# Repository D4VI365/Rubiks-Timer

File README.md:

# Rubiks Timer
I'm gonna build a timer to use with my rubiks cube, it will be powered by an esp32 and it will host a webpage to view the times registered.

The device is powered by a rechargable 2000mAh LiPo battery, it shows the time to the millisecond and the status of the timer with a strip of neopixels. There also are two phisical buttons for an easier access to deleting the time and adding a penality.

Full timer:

Electrical scheme:

PCB layout: 

Inernal components placement:

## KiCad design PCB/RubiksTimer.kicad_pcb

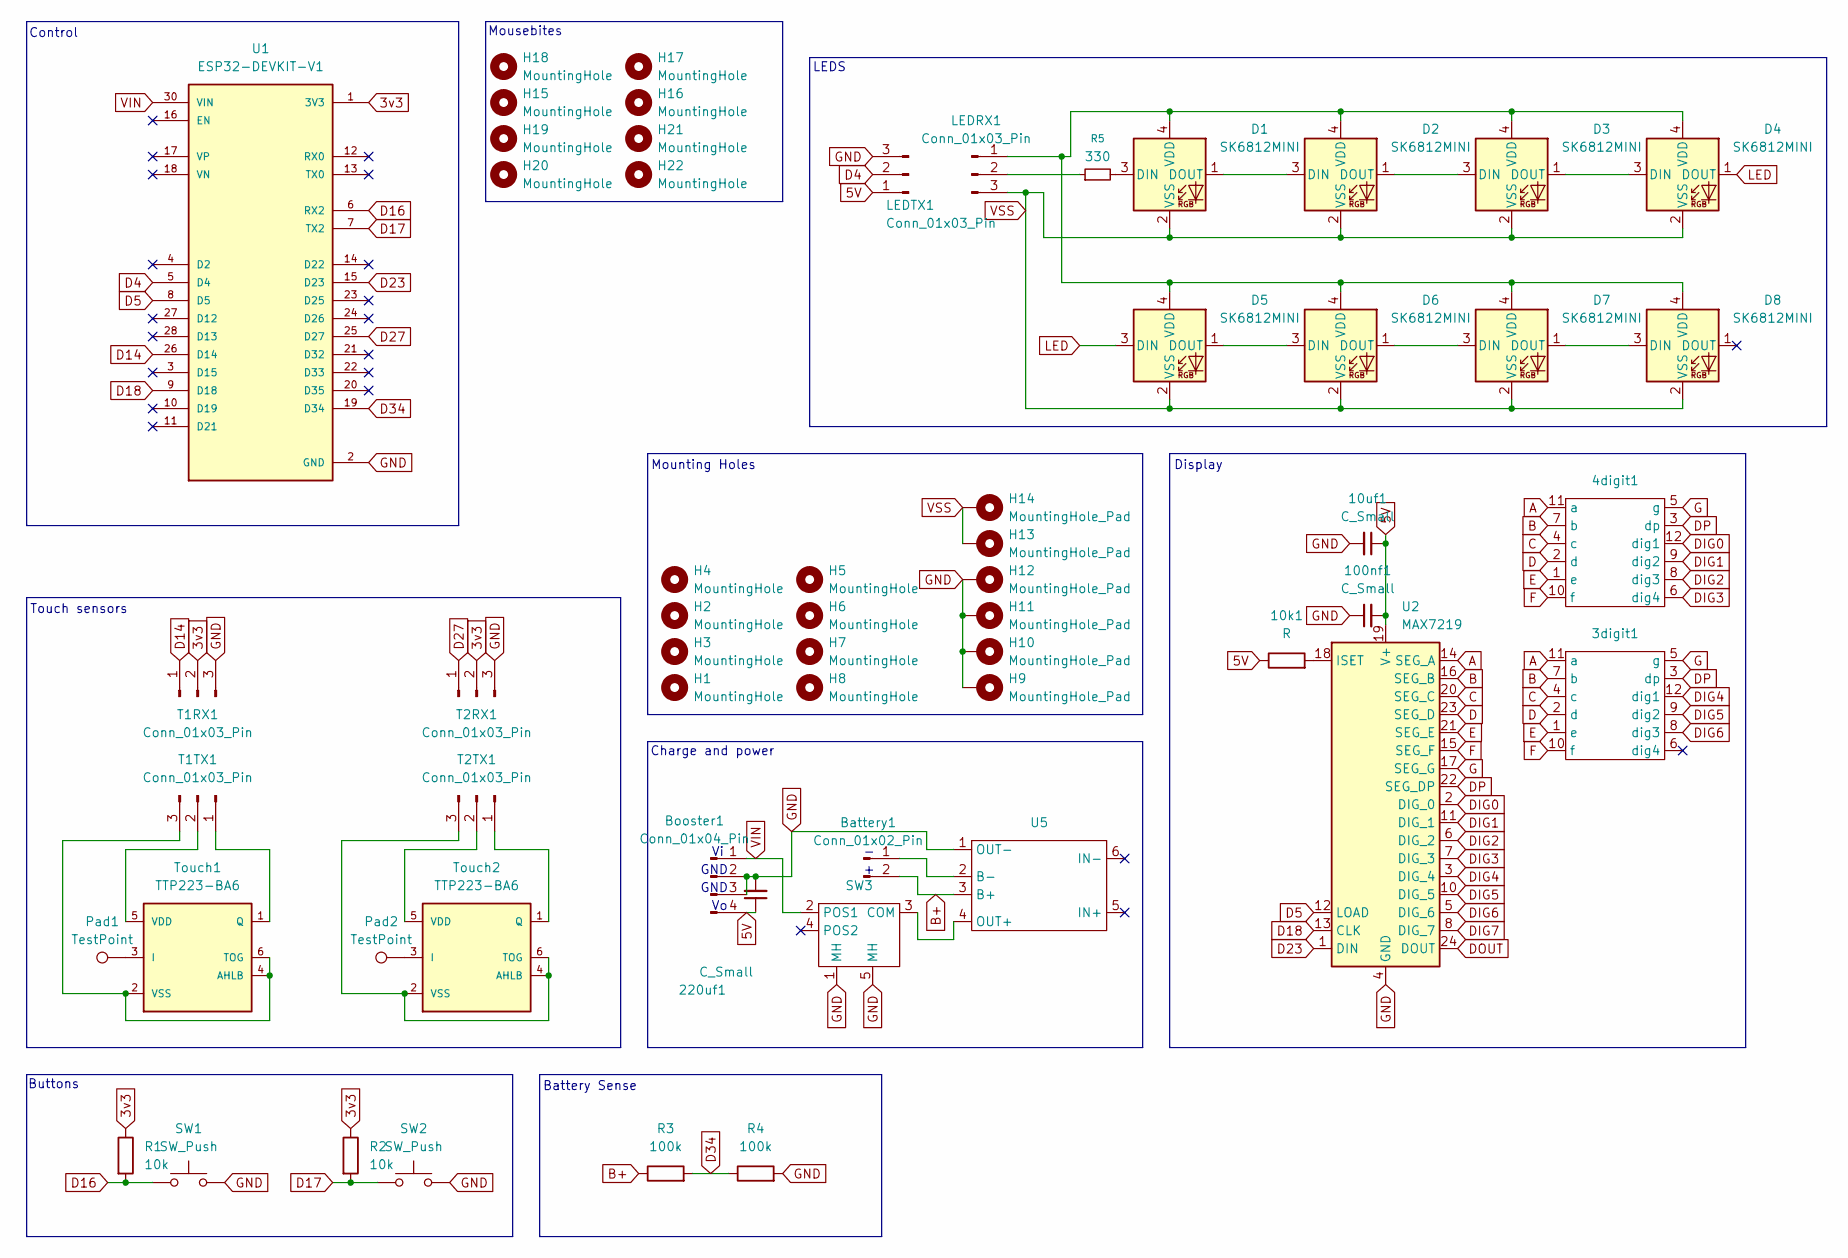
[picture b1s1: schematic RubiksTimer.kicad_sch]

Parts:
3digit1: 3dig CC display
4digit1: 4dig CC display
10k1: R; R_0805_2012Metric_Pad1.20x1.40mm_HandSolder
10uf1: C_Small; CP_Radial_D5.0mm_P2.00mm
100nf1: C_Small; C_Disc_D5.0mm_W2.5mm_P2.50mm
220uf1: C_Small; CP_Radial_D6.3mm_P2.50mm
Battery1: Conn_01x02_Pin; PinHeader_1x02_P2.54mm_Vertical
Booster1: Conn_01x04_Pin; PinHeader_1x04_P2.54mm_Vertical
D1, D2, D3, D4, D5, D6, D7, D8: SK6812MINI; MX_SK6812MINI-E
H1, H2, H3, H4, H5, H6, H7, H8: MountingHole; MountingHole_3.2mm_M3
H9, H10, H11, H12, H13, H14: MountingHole_Pad; MountingHole_3.2mm_M3_DIN965_Pad
H15, H16, H17, H18, H19, H20, H21, H22: MountingHole; Mousebite
LEDRX1: Conn_01x03_Pin; PinHeader_1x03_P2.54mm_Vertical
LEDTX1: Conn_01x03_Pin; PinHeader_1x03_P2.54mm_Vertical
Pad1, Pad2: TestPoint; 30x27pad
R1, R2: 10k; R_0805_2012Metric_Pad1.20x1.40mm_HandSolder
R3, R4: 100k; R_0805_2012Metric_Pad1.20x1.40mm_HandSolder
R5: 330; R_0805_2012Metric_Pad1.20x1.40mm_HandSolder
SW1, SW2: SW_Push; SW_Cherry_MX_1.00u_PCB
SW3: PinHeader_1x05_P2.00mm_Vertical
T1RX1, T1TX1, T2RX1, T2TX1: Conn_01x03_Pin; PinHeader_1x03_P2.54mm_Vertical
Touch1, Touch2: TTP223-BA6; SOT-23-6_Handsoldering
U1: ESP32-DEVKIT-V1; MODULE_ESP32_DEVKIT_V1; PARTREV N/A
U2: MAX7219; DIP-24_W7.62mm
U5: TP4056-protected

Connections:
3v3: R1.1, R2.1, T1RX1.2, T2RX1.2, U1.1 (3V3)
5V: 10k1.1, 10uf1.1, 100nf1.2, 220uf1.1, Booster1.4, LEDTX1.1, U2.19 (V+)
A: 3digit1.11 (a), 4digit1.11 (a), U2.14 (SEG_A)
B: 3digit1.7 (b), 4digit1.7 (b), U2.16 (SEG_B)
B+: Battery1.2, R3.1, U5.3 (B+)
C: 3digit1.4 (c), 4digit1.4 (c), U2.20 (SEG_C)
D: 3digit1.2 (d), 4digit1.2 (d), U2.23 (SEG_D)
D4: LEDTX1.2, U1.5 (D4)
D5: U1.8 (D5), U2.12 (LOAD)
D14: T1RX1.1, U1.26 (D14)
D16: R1.2, SW1.1, U1.6 (RX2)
D17: R2.2, SW2.1, U1.7 (TX2)
D18: U1.9 (D18), U2.13 (CLK)
D23: U1.15 (D23), U2.1 (DIN)
D27: T2RX1.1, U1.25 (D27)
D34: R3.2, R4.1, U1.19 (D34)
DIG0: 4digit1.12 (dig1), U2.2 (DIG_0)
DIG1: 4digit1.9 (dig2), U2.11 (DIG_1)
DIG2: 4digit1.8 (dig3), U2.6 (DIG_2)
DIG3: 4digit1.6 (dig4), U2.7 (DIG_3)
DIG4: 3digit1.12 (dig1), U2.3 (DIG_4)
DIG5: 3digit1.9 (dig2), U2.10 (DIG_5)
DIG6: 3digit1.8 (dig3), U2.5 (DIG_6)
DIG7: U2.8 (DIG_7)
DOUT: U2.24 (DOUT)
DP: 3digit1.3 (dp), 4digit1.3 (dp), U2.22 (SEG_DP)
E: 3digit1.1 (e), 4digit1.1 (e), U2.21 (SEG_E)
F: 3digit1.10 (f), 4digit1.10 (f), U2.15 (SEG_F)
G: 3digit1.5 (g), 4digit1.5 (g), U2.17 (SEG_G)
GND: 10uf1.2, 100nf1.1, 220uf1.2, Booster1.2, Booster1.3, H9.1 (1_1), H10.1 (1_1), H11.1 (1_1), H12.1 (1_1), LEDTX1.3, R4.2, SW1.2, SW2.2, SW3.1 (MH), SW3.5 (MH), T1RX1.3, T2RX1.3, U1.2 (GND), U1.29 (GND), U2.4 (GND), U2.9 (GND), U5.1 (OUT-)
LED: D4.1 (DOUT), D5.3 (DIN)
unnamed: Battery1.1, U5.2 (B-)
unnamed: D1.3 (DIN), R5.2
unnamed: D1.1 (DOUT), D2.3 (DIN)
unnamed: D1.4 (VDD), D2.4 (VDD), D3.4 (VDD), D4.4 (VDD), D5.4 (VDD), D6.4 (VDD), D7.4 (VDD), D8.4 (VDD), LEDRX1.1
unnamed: D2.1 (DOUT), D3.3 (DIN)
unnamed: D3.1 (DOUT), D4.3 (DIN)
unnamed: D5.1 (DOUT), D6.3 (DIN)
unnamed: D6.1 (DOUT), D7.3 (DIN)
unnamed: D7.1 (DOUT), D8.3 (DIN)
unnamed: LEDRX1.2, R5.1
unnamed: SW3.3 (COM), U5.4 (OUT+)
unnamed: T1TX1.1, Touch1.1 (Q)
unnamed: T1TX1.2, Touch1.5 (VDD)
unnamed: T1TX1.3, Touch1.2 (VSS), Touch1.4 (AHLB), Touch1.6 (TOG)
unnamed: T2TX1.1, Touch2.1 (Q)
unnamed: T2TX1.2, Touch2.5 (VDD)
unnamed: T2TX1.3, Touch2.2 (VSS), Touch2.4 (AHLB), Touch2.6 (TOG)
unnamed: Pad1.1 (1_1), Touch1.3 (I)
unnamed: Pad2.1 (1_1), Touch2.3 (I)
unnamed: 10k1.2, U2.18 (ISET)
VIN: Booster1.1, SW3.2 (POS1), U1.30 (VIN)
VSS: D1.2 (VSS), D2.2 (VSS), D3.2 (VSS), D4.2 (VSS), D5.2 (VSS), D6.2 (VSS), D7.2 (VSS), D8.2 (VSS), H13.1 (1_1), H14.1 (1_1), LEDRX1.3

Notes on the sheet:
LEDS
Mousebites
Display
Control
GND
Charge and power
Mounting Holes
Buttons
Touch sensors
Battery Sense

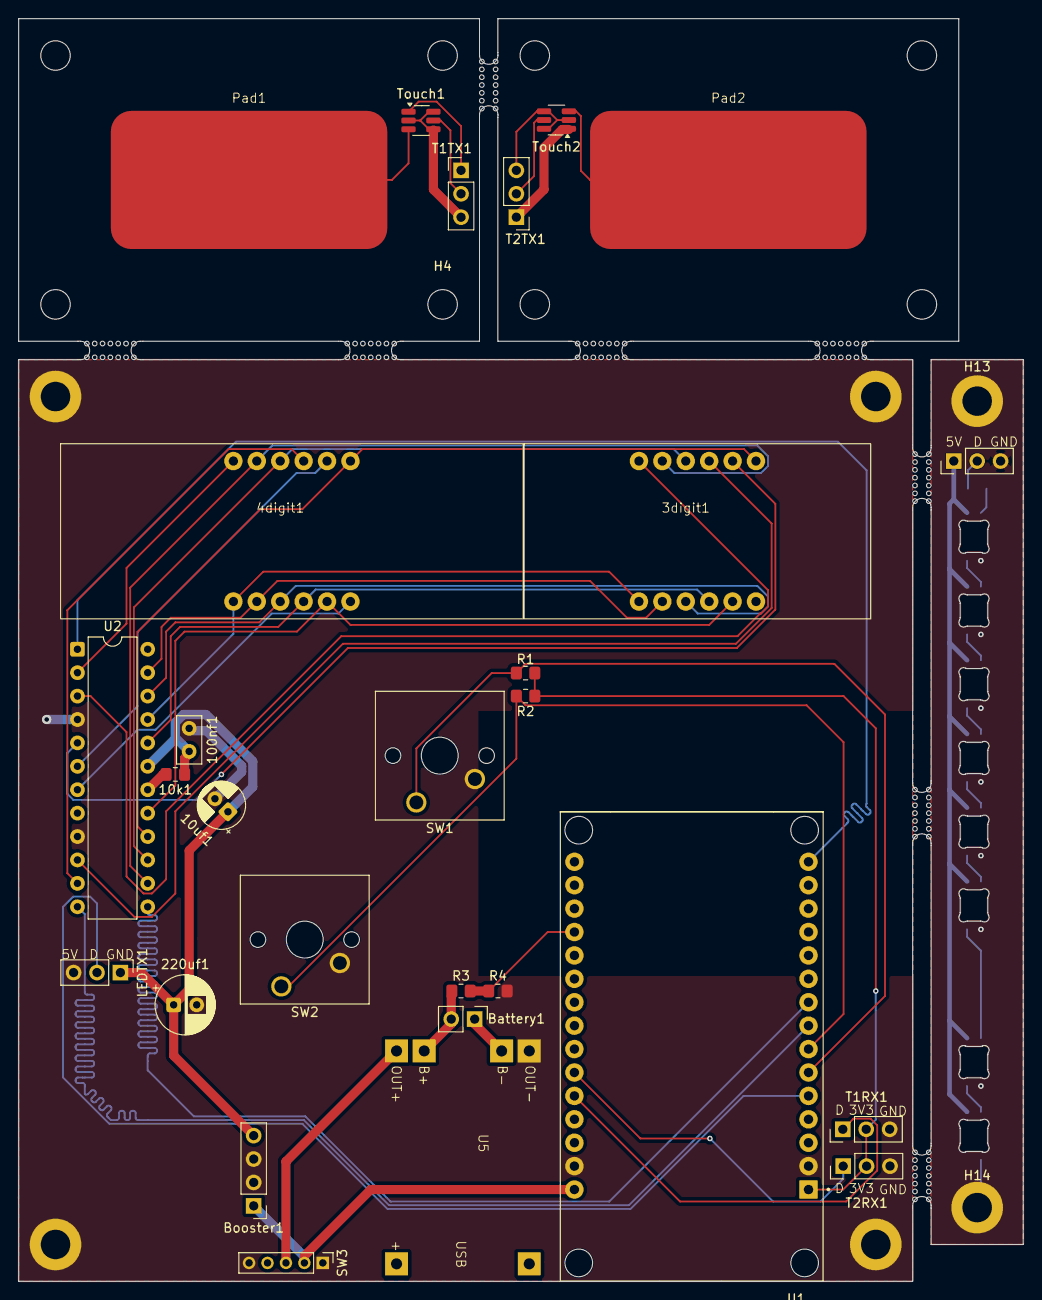
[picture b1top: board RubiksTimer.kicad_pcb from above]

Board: 2 copper layers, 109.0 x 137.0 mm, 59 parts (1 on the bottom side), 51 nets.

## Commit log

2026-04-26 initial push
